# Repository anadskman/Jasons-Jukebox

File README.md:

# Jasons-Jukebox

A minecraft style jukebox, uses a RFID reader and card(the disk). Then plays music through a DFPlayer. This is powered by a esp32-c3

### My Experience

I had a great time making this project, the easiest part in my opinion was designing the case. I added wood texures to the squares to make the pattern easier to see. The hardest part was the Code as im still new to it but I believe everything is correct.

### BOM
- 1x ESP32-C3 Super Mini
- 1x MFRC522 RFID reader
- 1x DFPlayer Mini
- 1x Speaker
- 1x Micro-SD card
- 1x Slide switch SPDT
- 2x M4 screws
- 2x M4 washers

- 1x Jasons-jukebox-code.ino
- 1x top-case.stl
- 4x side-case.stl
- 1x card-holder.stl

Schematic            |  PCB         |   Case
:-------------------------:|:-------------------------:|:-------------------------:|
 |  | 

# My Process
# 12/28/2025 - Made the schematic, footprints  

_Time spent: 2.0h_  

**I started by** adding everything into the schematic. I added an **esp32-c3-DevkitM-1**, **Slider Switch**, and imported a **Speaker**.
**What ended up taking so long** was trying to find symbols for the **MFRC522** and **DFPlayer**.
When I realized KiCad didn't have the symbols I tried to make them myself but then I realized there's probably some already made, so I downloaded them from SnapMagic.
**Afterwards** I wired everything together and assigned their footprints.

# 12/29/2025 3 PM - Made The PCB  

_Time spent: 0.8h_  

I **Routed** and **placed** the Components for the **PCB**.
This took a little **less than an hour** to do, I tried to keep in mind how I'd want it to sit into the jukebox so the RFID can still be used.
I'm thinking ill have it in the **top** and can be **taken out** if needed.

# 12/29/2025 6 PM - Remade Schematic and PCB, Started CAD Design  

_Time spent: 2.3h_  

I started with the **CAD Design** but Realised it would be better to use an **ESP-c3 super mini** board instead, so I remade the **schematic** wiring and the **PCB**. I also added **two m4 holes** on the PCB for **Mounting**.
Inside **Fusion 360** I uploaded the components and placed them on the PCB.
After that I Worked on the design for the **Case**.
I made the top with two slots on top, the bigger one for the PCB and the smaller one to actually insert the **RFID Card**.
Lastly I Made the side with **16x16 squares 6.563mm**. The outer squares i extruded **3mm**, then the pattern **2mm** and the rest **1mm**.
I added a **wood texture** to the design to make it easier to see.

# 1/1/2026 - Finished Case and Code  

_Time spent: 1.0h_  

I **finished** making the case and added a plate to hold the **RFID card**.
Afterwards I made the **Arduino code**, this took a good bit to do but wasn't horrible.
Then I uploaded everything to **GitHub**.

# 1/3/2026 - Made BOM  

_Time spent: 0.9h_  

I found all the parts in **aliexpress**, the **DFPlayer**, **RFID Set**, **Speakers**, **SD Card**, and **esp board**.
Then I made the **BOM** inside **google sheets** and added the **urls** and **total cost**.
I left out the **discounts** incase they **expire** before I order.

# 1/26/2026 - Parts Arrived(kinda)  

_Time spent: 2.6h_  

Everything execpt the pcb arrived so i tried connecting to a bread board a testing it.
I started by just testing the dfplayer and esp but it wasnt working so i spent a long ah time testing and i found out it was a dud so now i have to order a new one, probably off amazon so itll work.

the next day I tested the rfid and it wasnt gettting powered, i just had to solder headers on.

# 2/13/2026 - Soldered the PCB together  

_Time spent: 2.0h_  

I started by testing all the components once the new dfplayer arrived and it all worked well.
I think the other dfplayer either was a fault or I did something wrong, who knows.
After that I soldered the pcb together, turns out it was slightly wrong so i had to solder the vcc on for the rfid to 3v with wire and break the trace. I also had to break the trace and add the resistor for the RX pin on the dfplayer.

# 2/15/2026 - Fixed Cad  

_Time spent: 2.0h_  

I made the sides of the jukebox smaller to cut down on print time.

Unfortunally i had to add conners to make the case a little bigger as i already printed the sides by the time i realised.

I made the top look alot nicer and im taking advantage of the bottom being open by mounting the pcb from there with a small piece.  

# 2/20/2026 - Made the Case  

_Time spent: 2.5h_  

I started my 3d printing the case but I deciced to make the case smaller to cut down on print times
I printed 2 of the sides at 1 time and then the other two after.
while they were printing i was working on making the pcb fit as sizing down messed that up which i realised a little late but i redesigned the top to make it look more like the minecraft version and it looks a lot better.
I also noticed the pcb wouldnt fit so i had to add little conners to glue on.
The next day i painted everything, this was pretty slow but i think it was worth it.

_**I finished painting everything about an hour later.**_

After everything was painted, the top plate and sides, i glued it all together execpt the little mount i made for the pcb, ill have to line that up but i may change the design.

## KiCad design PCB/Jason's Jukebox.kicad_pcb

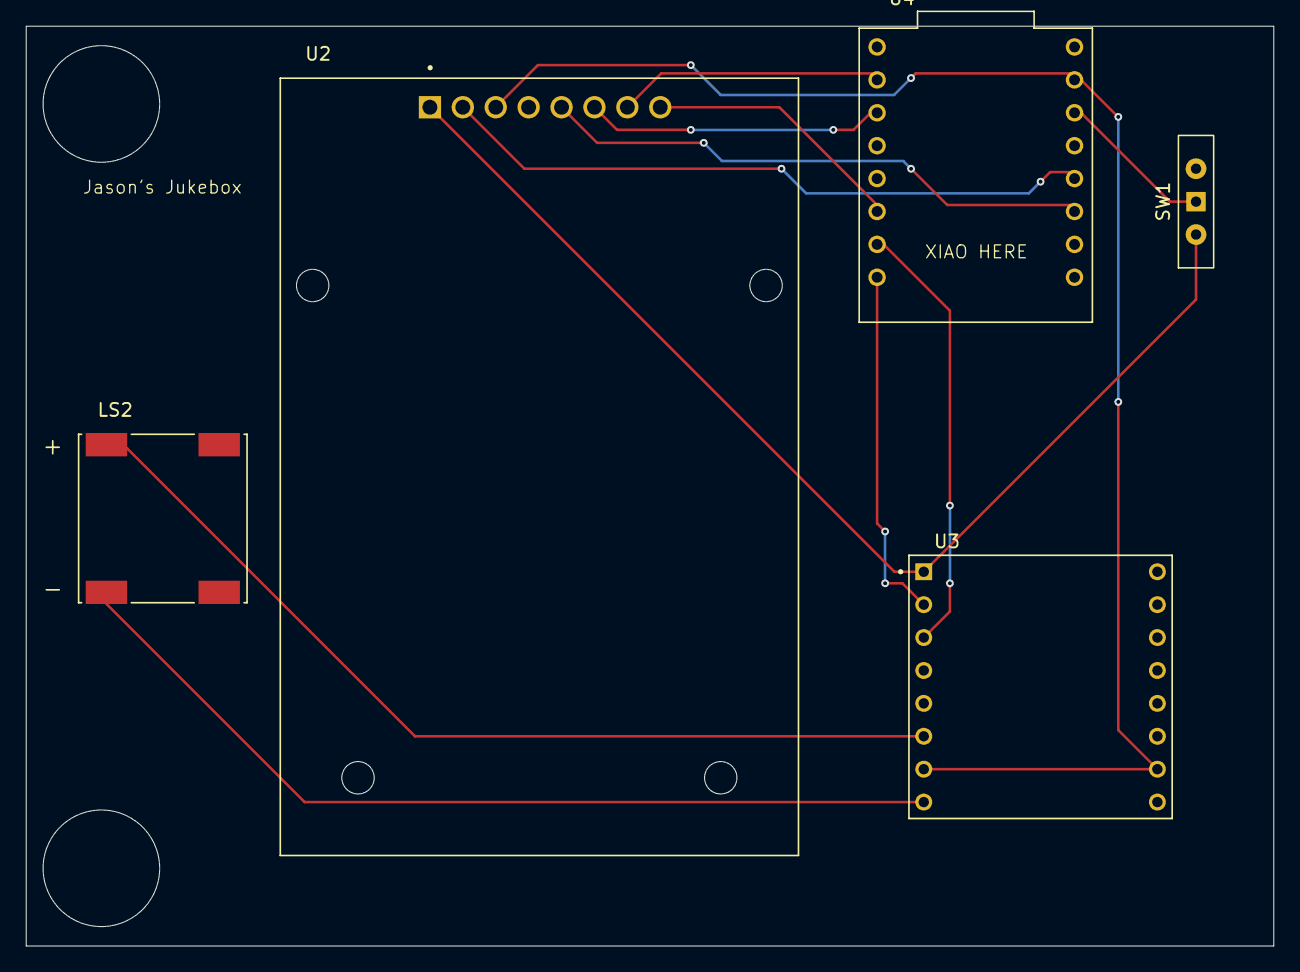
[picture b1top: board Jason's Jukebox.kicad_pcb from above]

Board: 2 copper layers, 96.3 x 71.0 mm, 5 parts (0 on the bottom side), 12 nets.

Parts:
LS2: Speaker; SPKR_KAAG13008-07C
SW1: Slider Switch; SW_Slide-03_Wuerth-WS-SLTV_10x2.5x6.4_P2.54mm
U2: RFID; MODULE_CEG006900
U3: DFPlayer; MODULE_DFR0299
U4: ESP32-C3_SUPERMINI_TH; MODULE_ESP32-C3_SUPERMINI_TH

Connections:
+3.3V: SW1.1 (B), U4.3.3 (3V3)
GND: U2.3 (GND), U3.7 (GND), U3.10 (GND), U4.G (GND)
unnamed: SW1.2 (C), U2.1 (VCC), U3.1 (VCC)
unnamed: U2.5 (MISO/SCL/TX), U4.2 (GPIO2)
unnamed: U2.6 (MOSI), U4.7 (GPIO7)
unnamed: U2.2 (RST), U4.3 (GPIO3)
unnamed: U2.7 (SCK), U4.6 (GPIO6)
unnamed: U2.8 (SS/SDA/RX), U4.10 (GPIO10)
unnamed: U3.2 (RX), U4.21 (GPIO21)
unnamed: LS2.P, U3.6 (SPK1)
unnamed: LS2.N, U3.8 (SPK2)
unnamed: U3.3 (TX), U4.20 (GPIO20)

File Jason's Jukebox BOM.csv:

Item,Description,Qty,Price(€),Url,Total
1pcs MFRC-522,RFID Reader and Card,1,1.68,https://www.aliexpress.com/item/32502259949.html,1.68
Mini Speakers 4ohm 3W,Speaker,2,1.51,https://www.aliexpress.com/item/1005010215641447.html,1.51
DFPlayer Mini,DFPlayer,1,0.89,https://www.aliexpress.com/item/1005008710314390.html,0.89
SD Card 2TB,SD Card,1,4.44,https://www.aliexpress.com/item/1005009550590600.html,4.44
ESP32-C3 Supermini,Dev Board,1,2.83,https://www.aliexpress.com/item/1005009495310442.html,2.83
,,,,Shipping,9.15
,,,,Total,20.5
